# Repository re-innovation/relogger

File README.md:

# Renewable Energy Data Logger

The RE-Logger is a multi-function renewable energy data-logger for remote logging of environmental and power data.
This is an Arduino-based data-logger desinged to have reasanable accuracy, be low-cost, suitable for use in remote areas (with no power available) and to be user-friendly to set-up and use.

The unit is designed to measure:

* Wind Speed - either from a hall-effect or pulse anemometer
* Wind Direction - from a variable resistance vane
* External Voltage - from a potential divider. NOT isolated.
* External Current - using a hall-effect sensor.
* RPM - from a wind turbine wild AC output
* There are 6 additional analog inputs which can be measured for a variety of sensors.
* An I2C port is available for I2C sensors
* A software serial port is available for GPS or other serial sensors

A 12-bit ADC is used to measure the analog data.
The data is stored on an SD card.
A DS3231 temperature-compensated Real Time Clock is used for accurate time measurement. 
There is an RGB indicator LED to dispalay errors.
The unit has two power supply options - either a solar power supply to recharge a LiPo battery, or with an external voltage of 0-40V DC or 0-60V DC (depending upon the IC used). Current consumption is designed to be minimised through power control and very low quiescent current devices.

The target price for the unit is a maximum of $50 including an enclosure.

This is based upon work with Wind Empowerment.

This repository contains:
* An overview of the project and functions
* The Schematics and PCB design files (KiCAD)
* The Arduino control code and associated libraries (To be Completed - NOT active)
* OLD Arduino code - Used in prototype testing
* Datasheets for all the components
* Instructions for use

# Sensors and Data

This logger can use different types of sensor attached to the inputs.

The set-up is defined on the config.txt file which must be included on the SD card.

The data required on the config.txt file is:

* Sample Time
* Sensor 1
* Sensor 2

Example config.txt file:

TO DO!

The types of sensor available are:

## Wind Speed Digital

These are conencted to a digital pin on the device.

Conversion factor required is the pulses per second to give 1m/s wind speed. 

eg: 0.6 pulse per second = 1m/s

If we read 15 pulses per second the wind speed is: 15/0.6 = 25m/s.

## Wind Speed Analog

This is connected to an analog pin.

The conversion factor is the voltage to wind speed factor.

eg. 0.1V per m/s

If we read a voltage of 0.6V then the wind speed is 0.6 / 0.1 = 6m/s

## Wind Direction

Wind direction uses a wind vane sensor with reed switches are used to introduce different resistors to the output line. Hence the output is a varying resistance, which can be measured using just one analogue pin and a potential divider.

The resistances are as follows, with all the resistors accurate to 1%. Using a potential divider of 10k for the lower resistor and a Vref of 3.3V, we can also calculate the analogue input values for each range:

* N = R1 = 33k Voltage reading = 0.76V
* NE = R2 = 8.2k Voltage reading = 1.81V
* E = R3 = 1k Voltage reading = 0.3V
* SE = R4 = 2.2k Voltage reading = 0.59V
* S = R5 = 3.9k Voltage reading = 0.92V
* SW = R6 = 16k Voltage reading = 2.03V
* W = R7 = 120k Voltage reading = 3.04V
* NW = R8 = 64.9k Voltage reading = 2.86V

## Voltage

Voltage is measured using a potential divider. R1 is the lower resistor, R2 is the top resistor.

So with R1 = 10k and R2 = 100k the real voltage is the measured voltage * (R1+R2)/(R1).

eg. V measured is 0.6V, the actual voltage will be 6.6V

We need to ensure headroom above the maximum required input voltage to ensure no damage happens to the analog input (which is protected by a zener diode). 

## Current

DC Current is measured by a range of different sensors. These generally give an output voltage which is linearly proportional to the current, but sometimes with an offset. More information here: 

https://www.re-innovation.co.uk/docs/dc-current-measurement/ 

https://www.re-innovation.co.uk/docs/acs756-current-measurements/

So we need to know the gradient and the offset for the sensor.

For the ACS758 (for example) the offset is 0.12 x Vsupply. If 5V is used as the supply voltage then the offset is 0.12 x 5 = 0.6V.
The ACS758 has a gradient of 60mV per A.

If we read 1.0V from the sensor then the conversion is: ((1.0V - offset)*1000)/ mV/A, so ((1.0-0.6)*1000)/60 = 6.66A 

The factor of 1000 converts the voltage to mV so the calculation works correctly.

The ACS756 has an offset of 1/2 of the supply voltage. The gradient is 40mV/A but this is ratio-metric. The supply for this unit should be 3.3V.

## Temperature Digital

The 1-wire temeprature sensor DS18B20 is used to measure the temperature.

This requires installation of a library to read the data from this sensor, which si returned in a specific format.

## Temperature Analog

Analog temperature sensors include thermistors and thermo-couples.

These sensors will also require specific libraries to convert from the voltage readign into a temperature, as thermistors are usually non-linear.

This section needs work to implement and a decision on which type of temperature sensors uses is required. 

# Testing in Athens

# To Do

* PCB redesign with no display. Fits onto solar LiPo unit if needed. - REMOVED DISPLAY
* PCB design with display shield for front
* Add protection on the input lines (1N4148 up to + and GND). Over AND undervoltage protection
* Config on SD card
* Test Nano power consumption
* Code full redesign
* Debounce in hardware - DONE
* HC12 Data connection to Wifi Logger unit - DONE

# Changes to make

* Sort out Vin connection - DONE
* Serial data connection without power (offset is affected by 5V voltage) - Use serial connector for this
* Debounce wih buffer/filter- NEED Buffer, DONE - Filter.
* Ground connection to SD card unit - DONE
* RC filter on the Current Measurement - DONE on prototype
* Sort out power supply issues (drop in voltage after readings made (SD write?)).
* Sort out accurate Vref on board
* Sort out Offset to store float as int? 
* Isolated voltage measurement?

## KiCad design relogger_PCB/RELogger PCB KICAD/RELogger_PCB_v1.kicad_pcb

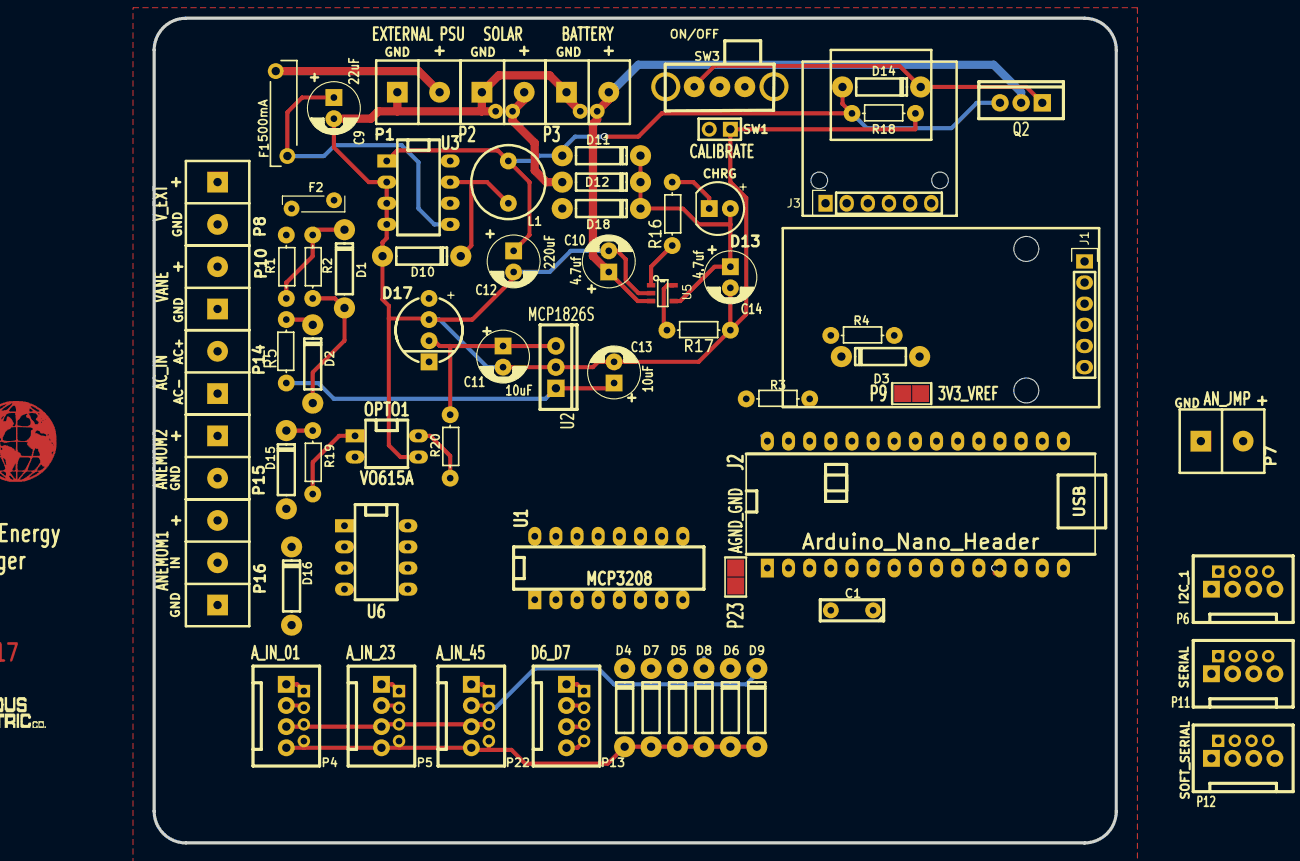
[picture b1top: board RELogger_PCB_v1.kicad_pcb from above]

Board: 2 copper layers, 115.6 x 99.1 mm, 70 parts (0 on the bottom side), 54 nets.

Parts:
C1: 100n; C1_wide_lg_pad
C9: 22uF; C_1V7_TH
C10, C14: 4.7uf; C_1V7_TH
C11, C13: 10uF; C_1V7_TH
C12: 220uF; C_1V7_TH
D1, D2, D3, D4, D5, D6, D7, D8, D9: 5V1; TH_Diode_1
D10: 1N5819; TH_Diode_1
D11, D12, D14, D18: D_Schottky; TH_Diode_1
D13: CHRG; TH_LED-5MM_larg_pad
D15: 1N4001; TH_Diode_1
D16: D; TH_Diode_1
D17: WS2811_EpiStar_8mm; TH_WS2811_LED_8mm
F1: 500mA; TH_MC36201_FUSE
F2: 100mA; TH_MC36188_FUSE
J1: RTC_MODULE; TH_RTC_MODULE
J2: Arduino_Nano_Header; NANO_DIP_30_600
J3: MICRO_SD; TH_SD_MODULE
L1: 330uH; TH_Inductor
LOGO1: CONN_1; CEC_Globe_10mm_FCU
LOGO2: CONN_1; TCEC_Words_13mm
OPTO1: VO615A; DIP-4_300_ELL
P1: EXTERNAL PSU; SIL-2_screw_terminal
P2: BATTERY; SIL_2_screw_+_JST_2mm
P3: SOLAR; SIL_2_screw_+_JST_2mm
P4: A_IN_01; SIL-4_Grove_SIL
P5: A_IN_23; SIL-4_Grove_SIL
P6: I2C_1; SIL-4_Grove_SIL
P7: AN_JMP; SIL-2_screw_terminal
P8: V_EXT; SIL-2_screw_terminal
P9: 3V3_VREF; SM_2_SLDR_JMP
P10: VANE; SIL-2_screw_terminal
P11: SERIAL; SIL-4_Grove_SIL
P12: SOFT_SERIAL; SIL-4_Grove_SIL
P13: D6_D7; SIL-4_Grove_SIL
P14: AC_IN; SIL-2_screw_terminal
P15: ANEMOM2; SIL-2_screw_terminal
P16: ANEMOM1; SIL-3_screw_terminal
P22: A_IN_45; SIL-4_Grove_SIL
P23: AGND_GND; SM_2_SLDR_JMP
Q2: RFU9110PBF; TO220_P_FET
R1: 470k; TH_Resistor_1
R2: 47k; TH_Resistor_1
R3, R4, R18: 100k; TH_Resistor_1
R5, R20: 10k; TH_Resistor_1
R16: 470; TH_Resistor_1
R17: 2k; TH_Resistor_1
R19: 1k; TH_Resistor_1
SW1: CALIBRATE; SIL-2_large_hole
SW3: ON/OFF; SW_SPDT_rapid_760271
U1: MCP3208; DIP-16__300_ELL
U2: MCP1826S; TO220_MCP1826S
U3: LM2574; DIP-8_300_ELL
U5: MCP73832; SM_SOT-23-5
U6: LM393; DIP-8_300_ELL

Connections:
+3.3V: C13.1, J3.1, P13.3, R5.1, U1.15, U2.3
/A0: D4.1, U1.3
/A1: D7.1, P4.2, U1.4
/A2: D5.1, U1.5
/A3: D8.1, P5.2, U1.6
/A4: D6.1, U1.7
/A5: D9.1, P22.2, U1.8
/A6: J2.25, P13.1
/A7: J2.26, P13.2
/AC_to_Freq/AC_IN+: D15.2, P14.2
/AC_to_Freq/AC_IN-: OPTO1.2, P14.1
/Arduino Uno/5v: D18.2, J2.27
/Arduino Uno/D8: J2.11, SW1.2
/Arduino Uno/RESET: J2.3, J2.28
/Arduino Uno/VREF: J2.18, P9.2
/CLK_ADC: J2.16, J3.4, U1.13
/CLK_INT: J1.5, J2.5
/CS_ADC: J2.12, U1.10
/DIN_ADC: J2.14, J3.3, U1.11
/DOUT_ADC: J2.15, J3.5, U1.12
/Hall_to_freq/Freq_OUT2: P7.1, U6.7
/IN_ACFREQ: J2.7, OPTO1.4, P7.2, R20.2
/IN_AN1: J2.6, U6.1
/LED_WS2811: D17.4, J2.22
/Power Supply/3V3_REF: J2.17, P9.1
/Power Supply/BATT+: C10.1, P2.2, Q2.2, U5.3
/Power Supply/EXTERNAL+: C9.1, F1.2, U3.5
/Power Supply/SOLAR+: D12.2, P3.2
/Rx: J2.2, P11.1
/Rx_SOFT: J2.21, P12.1
/SCLK: J1.4, J2.24, P6.1
/SDA: J1.3, J2.23, P6.2
/SD_CS: J2.13, J3.2
/Tx: J2.1, P11.2
/Tx_SOFT: J2.20, P12.2
/VANE: D2.1, P10.2, R5.2, U1.2
/VBATT: D3.1, J2.19, R3.2, R4.1
/VEXT: D1.1, R1.2, R2.1, U1.1
/Vss: C1.1, C11.1, D17.2, J1.2, P6.3, P11.3, P12.3, P16.3, R3.1, R20.1, SW3.2, U1.16, U2.1, U6.8
GND: C1.2, C9.2, C10.2, C11.2, C12.2, C13.2, C14.2, D10.2, D17.3, J1.1, J2.4, J2.29, J3.6, OPTO1.3, P1.1, P2.1, P3.1, P6.4, P11.4, P13.4, P15.2, P16.1, P23.1, R17.2, R18.2, SW1.1, U1.9, U2.2, U3.2, U3.3, U3.4, U5.2, U6.4
GNDA: D1.2, D2.2, D3.2, D4.2, D5.2, D6.2, D7.2, D8.2, D9.2, P4.4, P5.4, P8.2, P10.1, P22.4, P23.2, R2.2, R4.2, U1.14
unnamed: C12.1, D11.2, D14.2, L1.2, Q2.1, R18.1, U3.1
unnamed: C14.1, D11.1, D12.1, D13.2, D18.1, U5.4
unnamed: D10.1, L1.1, U3.7
unnamed: D13.1, R16.1
unnamed: D14.1, Q2.3, SW3.1
unnamed: D15.1, R19.1
unnamed: F1.1, P1.2
unnamed: F2.1, P8.1
unnamed: F2.2, R1.1
unnamed: OPTO1.1, R19.2
unnamed: P4.3, P5.3, P22.3
unnamed: R16.2, U5.1
unnamed: R17.1, U5.5

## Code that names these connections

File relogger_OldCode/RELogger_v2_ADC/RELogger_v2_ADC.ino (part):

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/************User variables and hardware allocation**********************************************/

/******* SD CARD*************/
#define SD_CS 10 // The SD card Chip Select pin 10

// SD file system object
SdFat sd;
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volatile long dataCounter = 0;  // This holds the number of seconds since the last data store

// ******** WS2811 LED**************************************/
#define LED_WS2811 A3
// Parameter 1 = number of pixels in strip
// Parameter 2 = Arduino pin number (most are valid)
// Parameter 3 = pixel type flags, add together as needed:
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#define battVoltagePin A0   // The battery voltage with a potential divider (100k//100k)
//#define voltagePin A2  // The external voltage with a potential divider (470k // 47k)
//#define current1Pin A3  // Current from a hall effect sensor
//#define vanePin A0      // The wind vane with a 10k pull DOWN

// We now read data from the ADC - so need to know which ADC lines to read
#define voltagePin  0  // The external voltage with a potential divider (470k // 47k) ADC 0
#define vanePin     1   // The wind vane with a 10k pull DOWN ADC 1
#define current1Pin 2  // Current from a hall effect sensor ADC 2


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  
  // make sure that the default chip select pin is set to
  // output, even if you don't use it:
  pinMode(SD_CS, OUTPUT);
  
  // see if the card is present and can be initialized:
  if (!sd.begin(SD_CS, SPI_HALF_SPEED)) {
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
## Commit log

2017-04-11 First commit of main info
2017-04-12 uploaded DS3231 library
2017-04-13 Schematic uploaded with Arduino Nano, SD Card connector and DS3231 connector
2017-04-13 Merge remote-tracking branch 'origin/master'
    # Conflicts:
    # relogger_PCB/RELogger PCB KICAD/AC_to_Freq.sch
    # relogger_PCB/RELogger PCB KICAD/ArduinoUno.sch
    # relogger_PCB/RELogger PCB KICAD/Hall_to_freq.sch
    # relogger_PCB/RELogger PCB KICAD/RELogger_PCB_v1-cache.lib
    # relogger_PCB/RELogger PCB KICAD/RELogger_PCB_v1.bak
2017-04-13 Update of file names
2017-04-13 Update of schematic
    By ML
2017-04-14 Schematic update and PCB initial run
2017-04-18 PCB Linking
2017-04-20 Small PCB updates
2017-04-20 BOM uploaded
2017-04-20 Small update
2017-04-20 Revert "Small update"
    This reverts commit fabb74e8d79b427a73ffd518ee6a77bfb9482e12.
    # Conflicts:
    # relogger_PCB/RELogger PCB KICAD/RELogger_PCB_v1.kicad_pcb-bak
2017-04-20 Re load of new PCB
2017-04-20 BOM done
2017-04-20 BOM updated
2017-06-12 update of PCB
2017-06-12 flow diagram
2017-06-20 Re-logger code
2017-06-22 Re-Logger code updated
2017-07-05 Old Arduino code added to athens branch
2017-07-05 Updated schmatic
    Debounce switches. Power control for all.
2017-07-05 Small updates
2017-07-06 Small updates
    Battery voltage measurement
2017-07-07 Sorted arduino code
    Just one version of the code
2017-11-05 Re formatting datasheets
2017-12-24 Updated new scehmatic.
    Still needs Freq conversion circuit. And 3.3V regulator

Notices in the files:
relogger_OldCode/RELogger_v2_ADC/RELogger_v2_ADC.ino:
Copyright (C)2015 Rinky-Dink Electronics, Henning Karlsen. All right reserved
